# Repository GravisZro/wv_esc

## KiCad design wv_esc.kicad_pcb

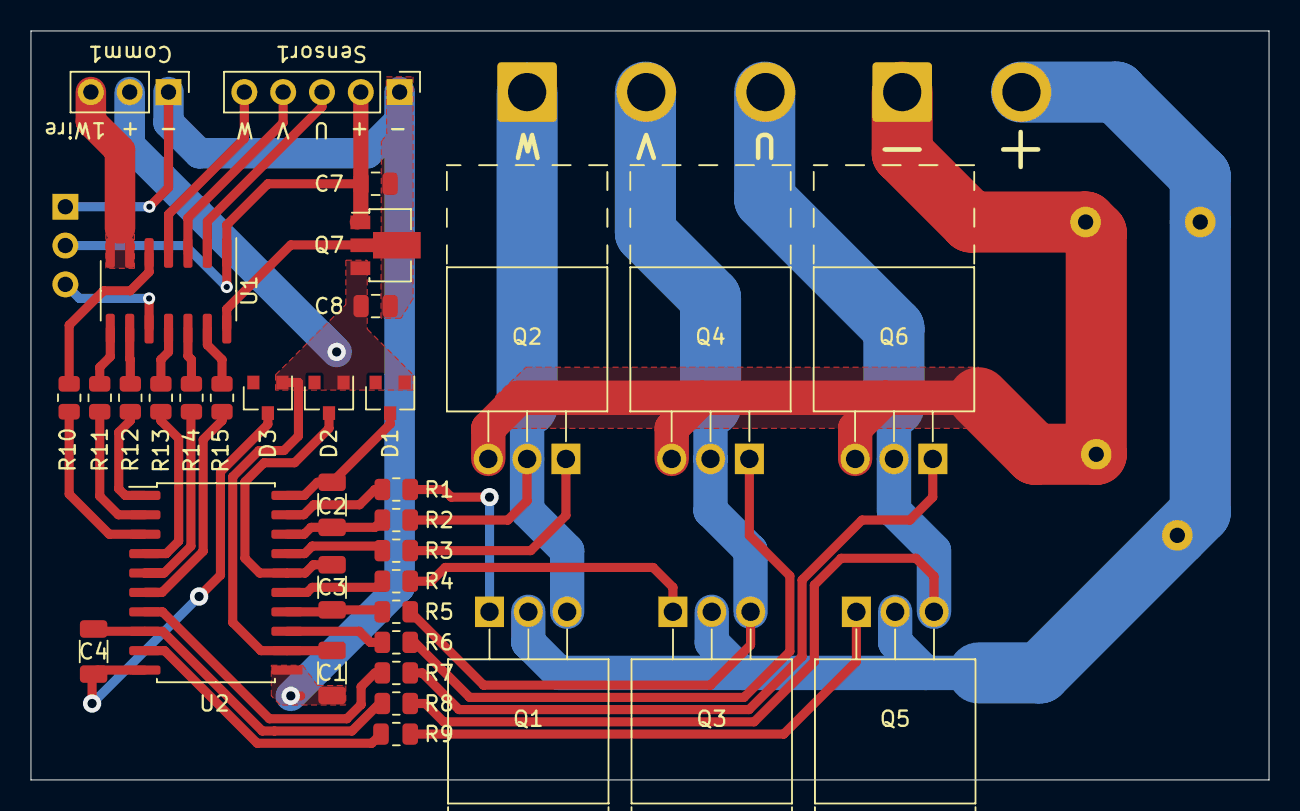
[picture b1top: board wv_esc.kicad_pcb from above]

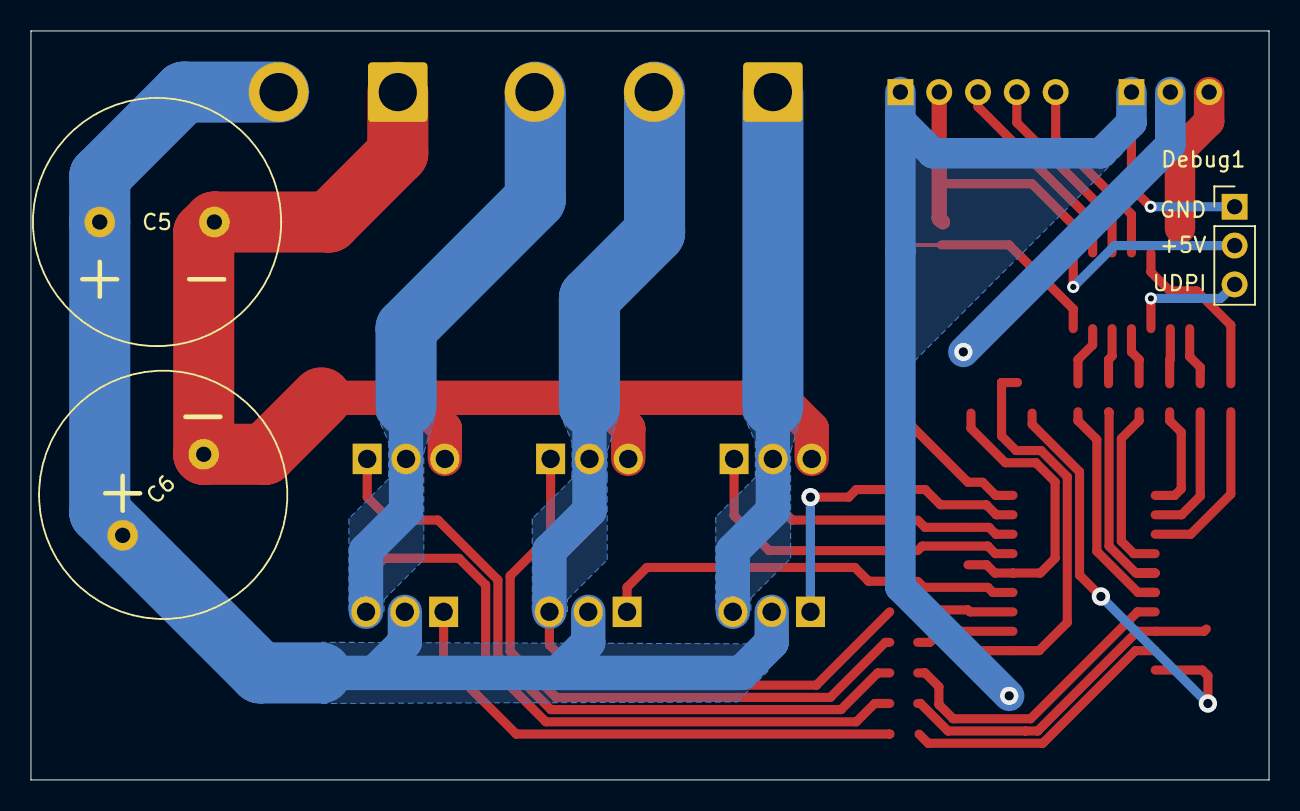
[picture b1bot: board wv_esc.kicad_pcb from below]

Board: 2 copper layers, 81.0 x 49.0 mm, 40 parts (3 on the bottom side), 43 nets.

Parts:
C1: 1μF, >15V; C_1206_3216Metric
C2, C3, C4: 2.2μF, 25V; C_1206_3216Metric
C5, C6: 220μF, 100V; C_Radial_D16.0mm_H25.0mm_P7.50mm
C7: 0.33μF, 10V; C_0805_2012Metric
C8: 0.1μF, 25V; C_0805_2012Metric
Comm1: Conn_01x03; PinHeader_1x03_P2.54mm_Vertical
D1, D2, D3: 100μA, 25V, <100ns recovery; D_SOT-23_ANK
Debug1: Conn_01x03; PinHeader_1x03_P2.54mm_Vertical
J1: Conn_01x02; SolderWire-2sqmm_1x02_P7.8mm_D2mm_OD3.9mm
J3: Conn_01x03; SolderWire-2sqmm_1x03_P7.8mm_D2mm_OD3.9mm
Q1, Q2, Q3, Q4, Q5, Q6: IRF135B203; TO-220F-3_Horizontal_TabUp
Q7: AS78LXX; SOT-89-3
R1, R2, R3, R4, R5, R6, R7, R8, R9: 4.7Ω; R_0805_2012Metric
R10, R11, R12, R13, R14, R15: 301Ω; R_0805_2012Metric
Sensor1: Conn_01x05; PinHeader_1x05_P2.54mm_Vertical
U1: ATtiny204-SS; SOIC-14_3.9x8.7mm_P1.27mm
U2: IRS2334; SOIC-20W_7.5x12.8mm_P1.27mm

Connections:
14V: C1.1, C8.1, Comm1.2, D1.2, D2.2, D3.2, Q7.3, U2.12
+5V: C7.2, Debug1.2, Q7.1, Sensor1.2, U1.1
+BATT: C5.1, C6.1, J1.2, Q1.2, Q3.2, Q5.2
-BATT: C5.2, C6.2, J1.1, Q2.3, Q4.3, Q6.3
/Driver and MOSFETS/MOSFET pair 1/high: R1.2, U2.19
/Driver and MOSFETS/MOSFET pair 1/load: C2.2, R2.2, U2.18
/Driver and MOSFETS/MOSFET pair 1/low: R3.2, U2.17
/Driver and MOSFETS/MOSFET pair 2/high: R4.2, U2.15
/Driver and MOSFETS/MOSFET pair 2/load: C3.2, R5.2, U2.14
/Driver and MOSFETS/MOSFET pair 2/low: R6.2, U2.13
/Driver and MOSFETS/MOSFET pair 3/high: R7.2, U2.9
/Driver and MOSFETS/MOSFET pair 3/load: C4.2, R8.2, U2.8
/Driver and MOSFETS/MOSFET pair 3/low: R9.2, U2.7
/Driver and MOSFETS/high_1: R12.1, U2.1
/Driver and MOSFETS/high_2: R10.1, U2.3
/Driver and MOSFETS/high_3: R14.1, U2.5
/Driver and MOSFETS/low_1: R11.1, U2.2
/Driver and MOSFETS/low_2: R13.1, U2.4
/Driver and MOSFETS/low_3: R15.1, U2.6
/Driver and MOSFETS/motor_output_1: J3.1, Q1.3, Q2.2, R2.1
/Driver and MOSFETS/motor_output_2: J3.2, Q3.3, Q4.2, R5.1
/Driver and MOSFETS/motor_output_3: J3.3, Q5.3, Q6.2, R8.1
GND: C1.2, C7.1, C8.2, Comm1.1, Debug1.1, Q7.2, Sensor1.1, U1.14, U2.11
unnamed: C2.1, D1.1, U2.20
unnamed: C3.1, D2.1, U2.16
unnamed: C4.1, D3.1, U2.10
unnamed: Comm1.3, U1.6, U1.7
unnamed: Debug1.3, U1.10
unnamed: Q1.1, R1.1
unnamed: Q2.1, R3.1
unnamed: Q3.1, R4.1
unnamed: Q4.1, R6.1
unnamed: Q5.1, R7.1
unnamed: Q6.1, R9.1
unnamed: R10.2, U1.5
unnamed: R11.2, U1.8
unnamed: R12.2, U1.9
unnamed: R13.2, U1.11
unnamed: R14.2, U1.12
unnamed: R15.2, U1.13
unnamed: Sensor1.3, U1.2
unnamed: Sensor1.4, U1.3
unnamed: Sensor1.5, U1.4

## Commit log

2021-09-30 initial upload
2021-09-30 add layout file
2021-10-02 use sheet for 5V regulator
2021-10-02 update images
